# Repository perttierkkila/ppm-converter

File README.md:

ppm-converter
=============

PWM/S-bus to PPM -converter

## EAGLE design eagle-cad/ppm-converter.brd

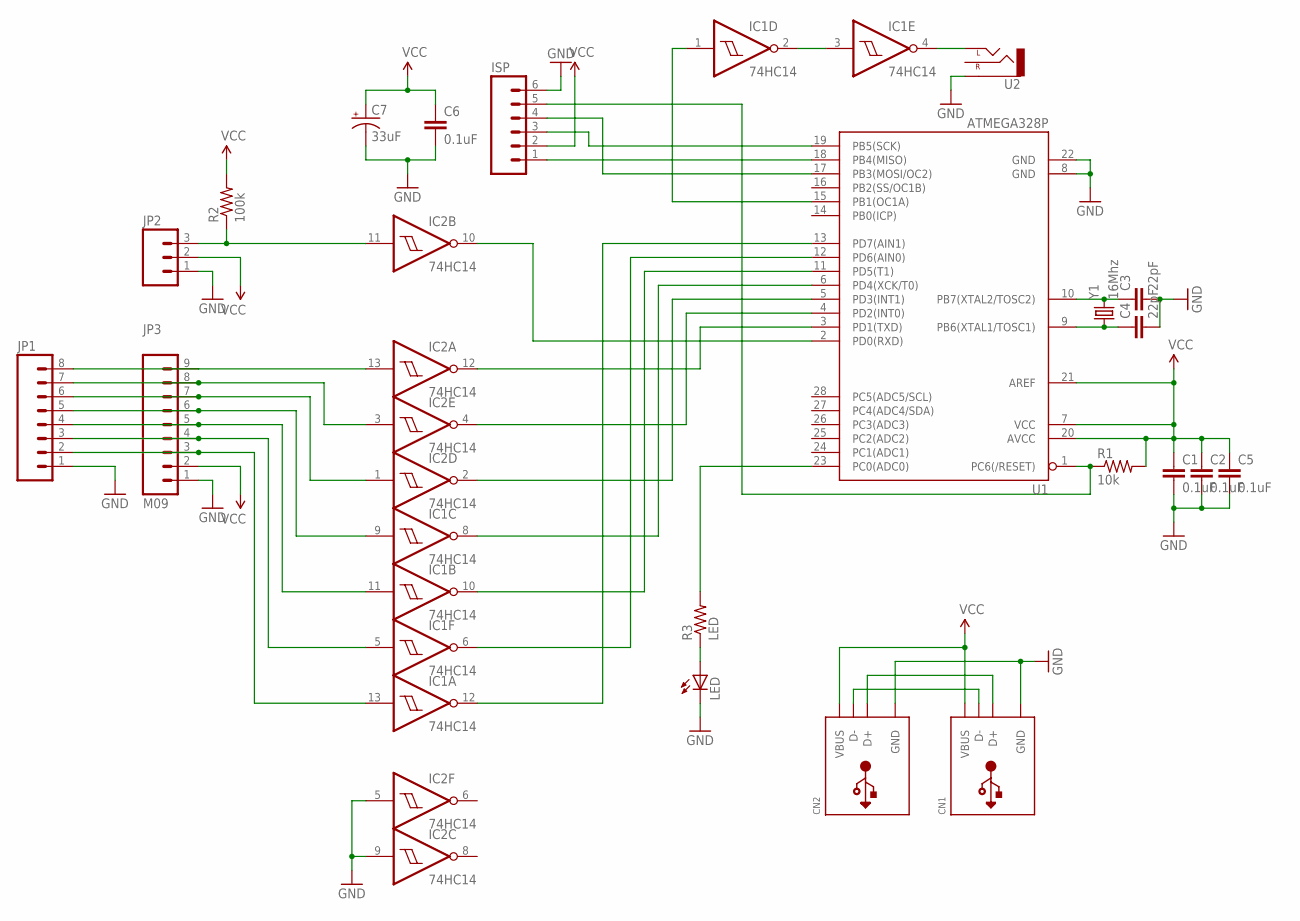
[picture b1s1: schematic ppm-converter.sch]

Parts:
C1, C2, C5, C6: 0.1uF; CAP-PTH-SMALL
C3, C4: 22pF; CAP-PTH-SMALL
C7: 33uF; CPOL-RADIAL-100UF-25V
CN1, CN2: USB_TYPEAPTHFML; USB_HOST-PTH
IC1, IC2: 74HC14; DIL14
ISP: M06SIP; 1X06
JP1: M081X08; 1X08
JP2: M03PTH; 1X03
JP3: M09; 1X09
LED: LED5MM-KIT
R1: 10k; AXIAL-0.3
R2: 100k; AXIAL-0.3
R3: LED; AXIAL-0.3
U1: ATMEGA328P; DIL28-3
U2: AUDIO-JACKPTH; AUDIO-JACK
Y1: 16Mhz; HC49US

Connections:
GND: C1.2, C2.2, C3.2, C4.2, C5.2, C6.2, C7.2 (-), CN1.GND, CN2.GND, IC1.7 (GND), IC2.5 (I), IC2.7 (GND), IC2.9 (I), ISP.6, JP1.1, JP2.1, JP3.1, LED.K (C), U1.8 (GND), U1.22 (GND), U2.SLEEVE
unnamed: IC1.2 (O), IC1.3 (I)
unnamed: CN1.D-, CN2.D-
unnamed: CN1.D+, CN2.D+
unnamed: ISP.5, R1.P$1 (1), U1.1 (PC6(/RESET))
unnamed: C3.1, U1.10 (PB7(XTAL2/TOSC2)), Y1.2
unnamed: C4.1, U1.9 (PB6(XTAL1/TOSC1)), Y1.1
unnamed: IC2.2 (O), U1.5 (PD3(INT1))
unnamed: IC1.4 (O), U2.TIP (LEFT)
unnamed: IC2.13 (I), JP1.8, JP3.9
unnamed: IC2.3 (I), JP1.7, JP3.8
unnamed: IC2.1 (I), JP1.6, JP3.7
unnamed: IC1.9 (I), JP1.5, JP3.6
unnamed: IC1.11 (I), JP1.4, JP3.5
unnamed: IC1.5 (I), JP1.3, JP3.4
unnamed: IC1.13 (I), JP1.2, JP3.3
unnamed: IC2.11 (I), JP2.3, R2.P$1 (1)
unnamed: IC2.10 (O), U1.2 (PD0(RXD))
unnamed: ISP.1, U1.18 (PB4(MISO))
unnamed: IC2.12 (O), U1.3 (PD1(TXD))
unnamed: IC2.4 (O), U1.4 (PD2(INT0))
unnamed: LED.A, R3.P$1 (1)
unnamed: IC1.8 (O), U1.6 (PD4(XCK/T0))
unnamed: IC1.10 (O), U1.11 (PD5(T1))
unnamed: IC1.6 (O), U1.12 (PD6(AIN0))
unnamed: IC1.12 (O), U1.13 (PD7(AIN1))
unnamed: IC1.1 (I), U1.15 (PB1(OC1A))
unnamed: ISP.3, U1.19 (PB5(SCK))
unnamed: ISP.4, U1.17 (PB3(MOSI/OC2))
unnamed: R3.P$2 (2), U1.23 (PC0(ADC0))
VCC: C1.1, C2.1, C5.1, C6.1, C7.1 (+), CN1.VBUS, CN2.VBUS, IC1.14 (VCC), IC2.14 (VCC), ISP.2, JP2.2, JP3.2, R1.P$2 (2), R2.P$2 (2), U1.7 (VCC), U1.20 (AVCC), U1.21 (AREF)

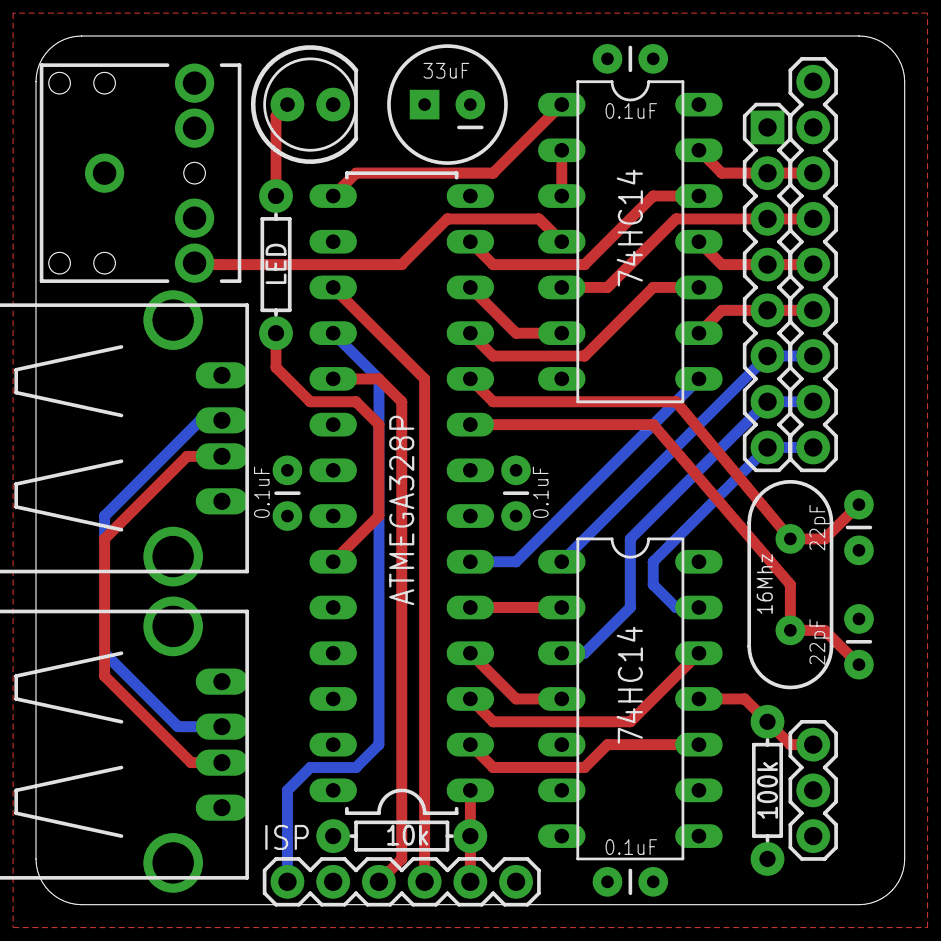
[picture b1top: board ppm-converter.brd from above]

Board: 2 copper layers, 48.3 x 48.3 mm, 22 parts (0 on the bottom side), 31 nets.

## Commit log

2013-02-20 Added Eagle schema + board
2013-02-25 Swapped pin texts to other side for better readibility
2013-04-04 Added ISP-header
2013-04-04 Added led+resistor, finetuning some titles
2013-04-04 Changed version -> revision, added 0.1uF cap
2013-04-04 A bit smaller board
2013-04-04 Minor fixes
2013-04-05 Finetuning for r02

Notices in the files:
parts and their libraries:
SparkFun-DigitalIC: Licensing: CC v3.0 Share-Alike You are welcome to use this library for commercial purposes.
microbuilder: This work is placed in the public domain, and may be freely used for commercial and non-commercial work with the following conditions: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
